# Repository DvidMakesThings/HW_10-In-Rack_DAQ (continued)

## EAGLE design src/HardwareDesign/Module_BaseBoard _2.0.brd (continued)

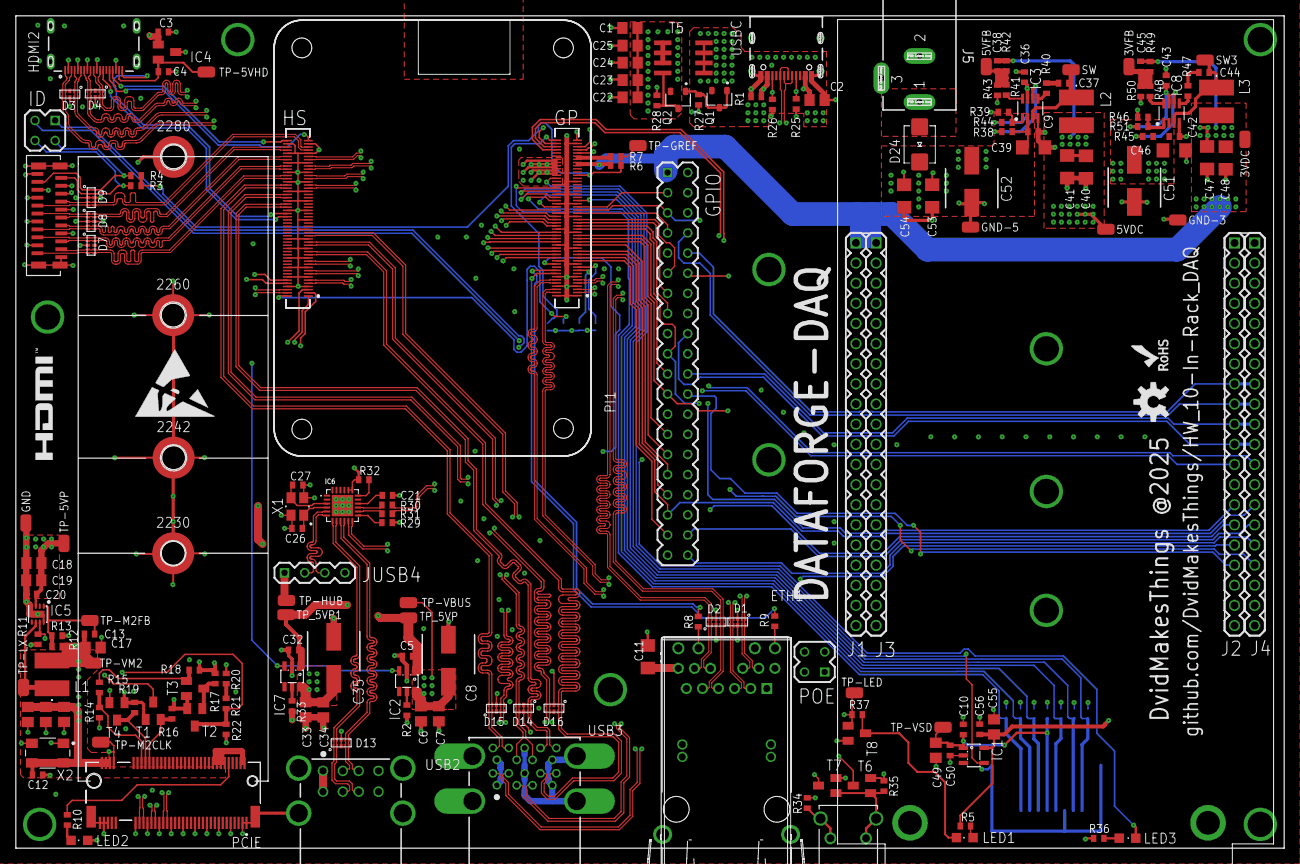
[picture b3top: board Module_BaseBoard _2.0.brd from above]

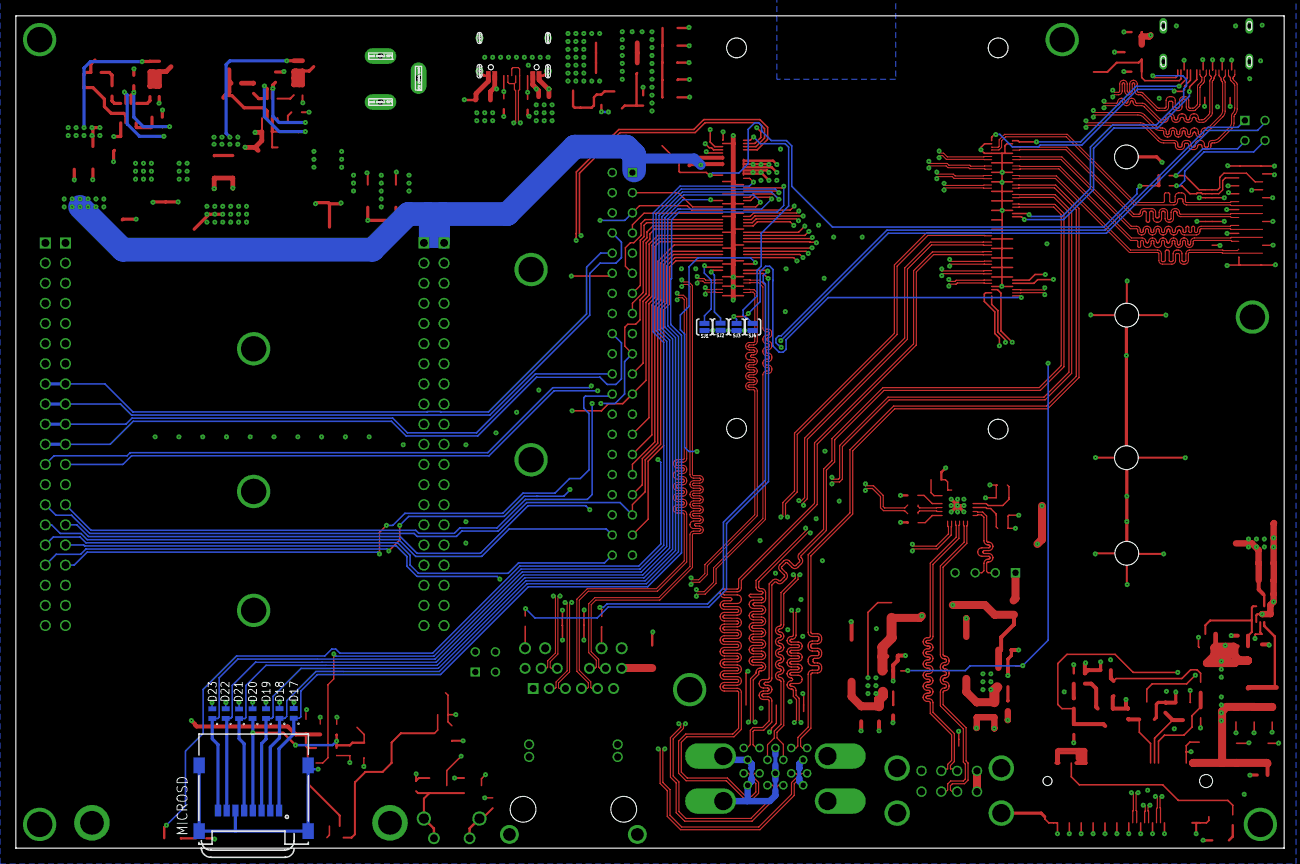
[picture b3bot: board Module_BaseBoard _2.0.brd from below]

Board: 6 copper layers, 160.0 x 105.0 mm, 198 parts (12 on the bottom side), 177 nets.

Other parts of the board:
U$1: ESD_10.00
U$2: OSHW-LOGO-M
U$3: ROHS_LOGO_0.18_IN

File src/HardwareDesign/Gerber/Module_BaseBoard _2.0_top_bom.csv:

Comment,Designator,Footprint,LCSC Part #
,IC6,QFN24,
,LED2,CHIPLED_0805,
,PI1,CM5,
0R,R6,0402,
1K,R5 R10 R34 R35 R36,0402,
2.2K,R16,0402,
2.2K 1%,R1 R3 R4 R13,0402,
2.2R,R30 R31,0402,
3.6K 1%,R21,0402,
4.2uH,L3,SRR5228A,
4.7nF,C13,C0402,
4.9uH,L2,SRR5228A,
6.8K 1%,R22,0402,
7.5K,R43 R46,0402,
9.09K,R39,0402,
10K,R14 R17 R18 R19,0402,
10K 1%,R12,0402,
10R,R40 R47,0402,
10pF,C26 C27,C0402,
10uF,C2 C6 C7 C14 C15 C16 C17 C18 C19 C23 C24 C25 C33 C34 C49,C0805,
10uF,C53,C1206,
10uF,C55,C0805,
12.7K,R50,0402,
12MHz,X1,WE-XTAL_CFPX-180,
15K 1%,R2 R33,0402,
20K,R41,0402,
22uF,C22,C0805,
22uF - 10V,C40 C41 C47 C48,C1206,
22uF 25V,C39 C46,C1206,
33K,R48,0402,
33pF,C38 C45,0402,
40.2K,R42 R49,0402,
100K,R27 R32 R44 R51,0402,
100K 1%,R11,0402,
100nF,C1,C0805,
100nF,C3 C4 C5,C0402,
100nF,C9,0402,
100nF,C10,C0402,
100nF,C11,C1206,
100nF,C12 C20 C21 C32,C0402,
100nF,C36 C37 C42 C43 C44,0402,
100nF,C50,C0402,
100nF,C54,C1206,
100nF,C56,C0402,
100uF,C51 C52,100UF-16V,
100uF 16V,C8 C35,100UF-16V,
470K,R28,0402,
470R,R8 R9,0402,
499K,R38 R45,0402,
629722000214,USBC,629722000214,
685119136923,HDMI2,685119136923,
AO4407A,T5,SO8,
AP3441SHE-7B,IC5,SON50P201X201X56-9T90X170N,
AP22653W6,IC2 IC7,SOT23-6,
BSS138,T1 T2 T3 T4 T6 T7 T8,SOT23,
CRYSTAL,X2,OSCCC500X320X130,
DNI,R7,0402,
FH12-22S-0.5SVA,DISP0,FH12-22S-0.5SH,
Green,LED1 LED3,CHIPLED_0805,
L,L1,SRR5228A,
M.2,PCIE,PCIE_M.2,
M2 x 1mm,2230 2242 2260 2280,WA-SMSI_9774010243,
MMBT3906,Q1 Q2,SOT23,
MP2315GJ-Z,IC3,SOT65P280X110-8N,
MP2315S ,IC8,SOT65P280X110-8N,
NC,R15 R20 R25 R26 R29 R37,0402,
RT9742GGJ,IC1,SOT23-5,
RT9742NGV,IC4,SOT23,
SS54B,D24,SMB,
TP,3VDC 3VFB 5VDC 5VFB GND GND-3 GND-5 SW SW3 TP-5VHD TP-5VP TP-GREF TP-HUB TP-LED TP-LX TP-M2CLK TP-M2FB TP-VBUS TP-VM2 TP-VSD TP_5VP TP_5VP1,TP,
TPD4EUSB30,D1 D2 D3 D4 D7 D8 D9 D13 D14 D15 D16,USON,

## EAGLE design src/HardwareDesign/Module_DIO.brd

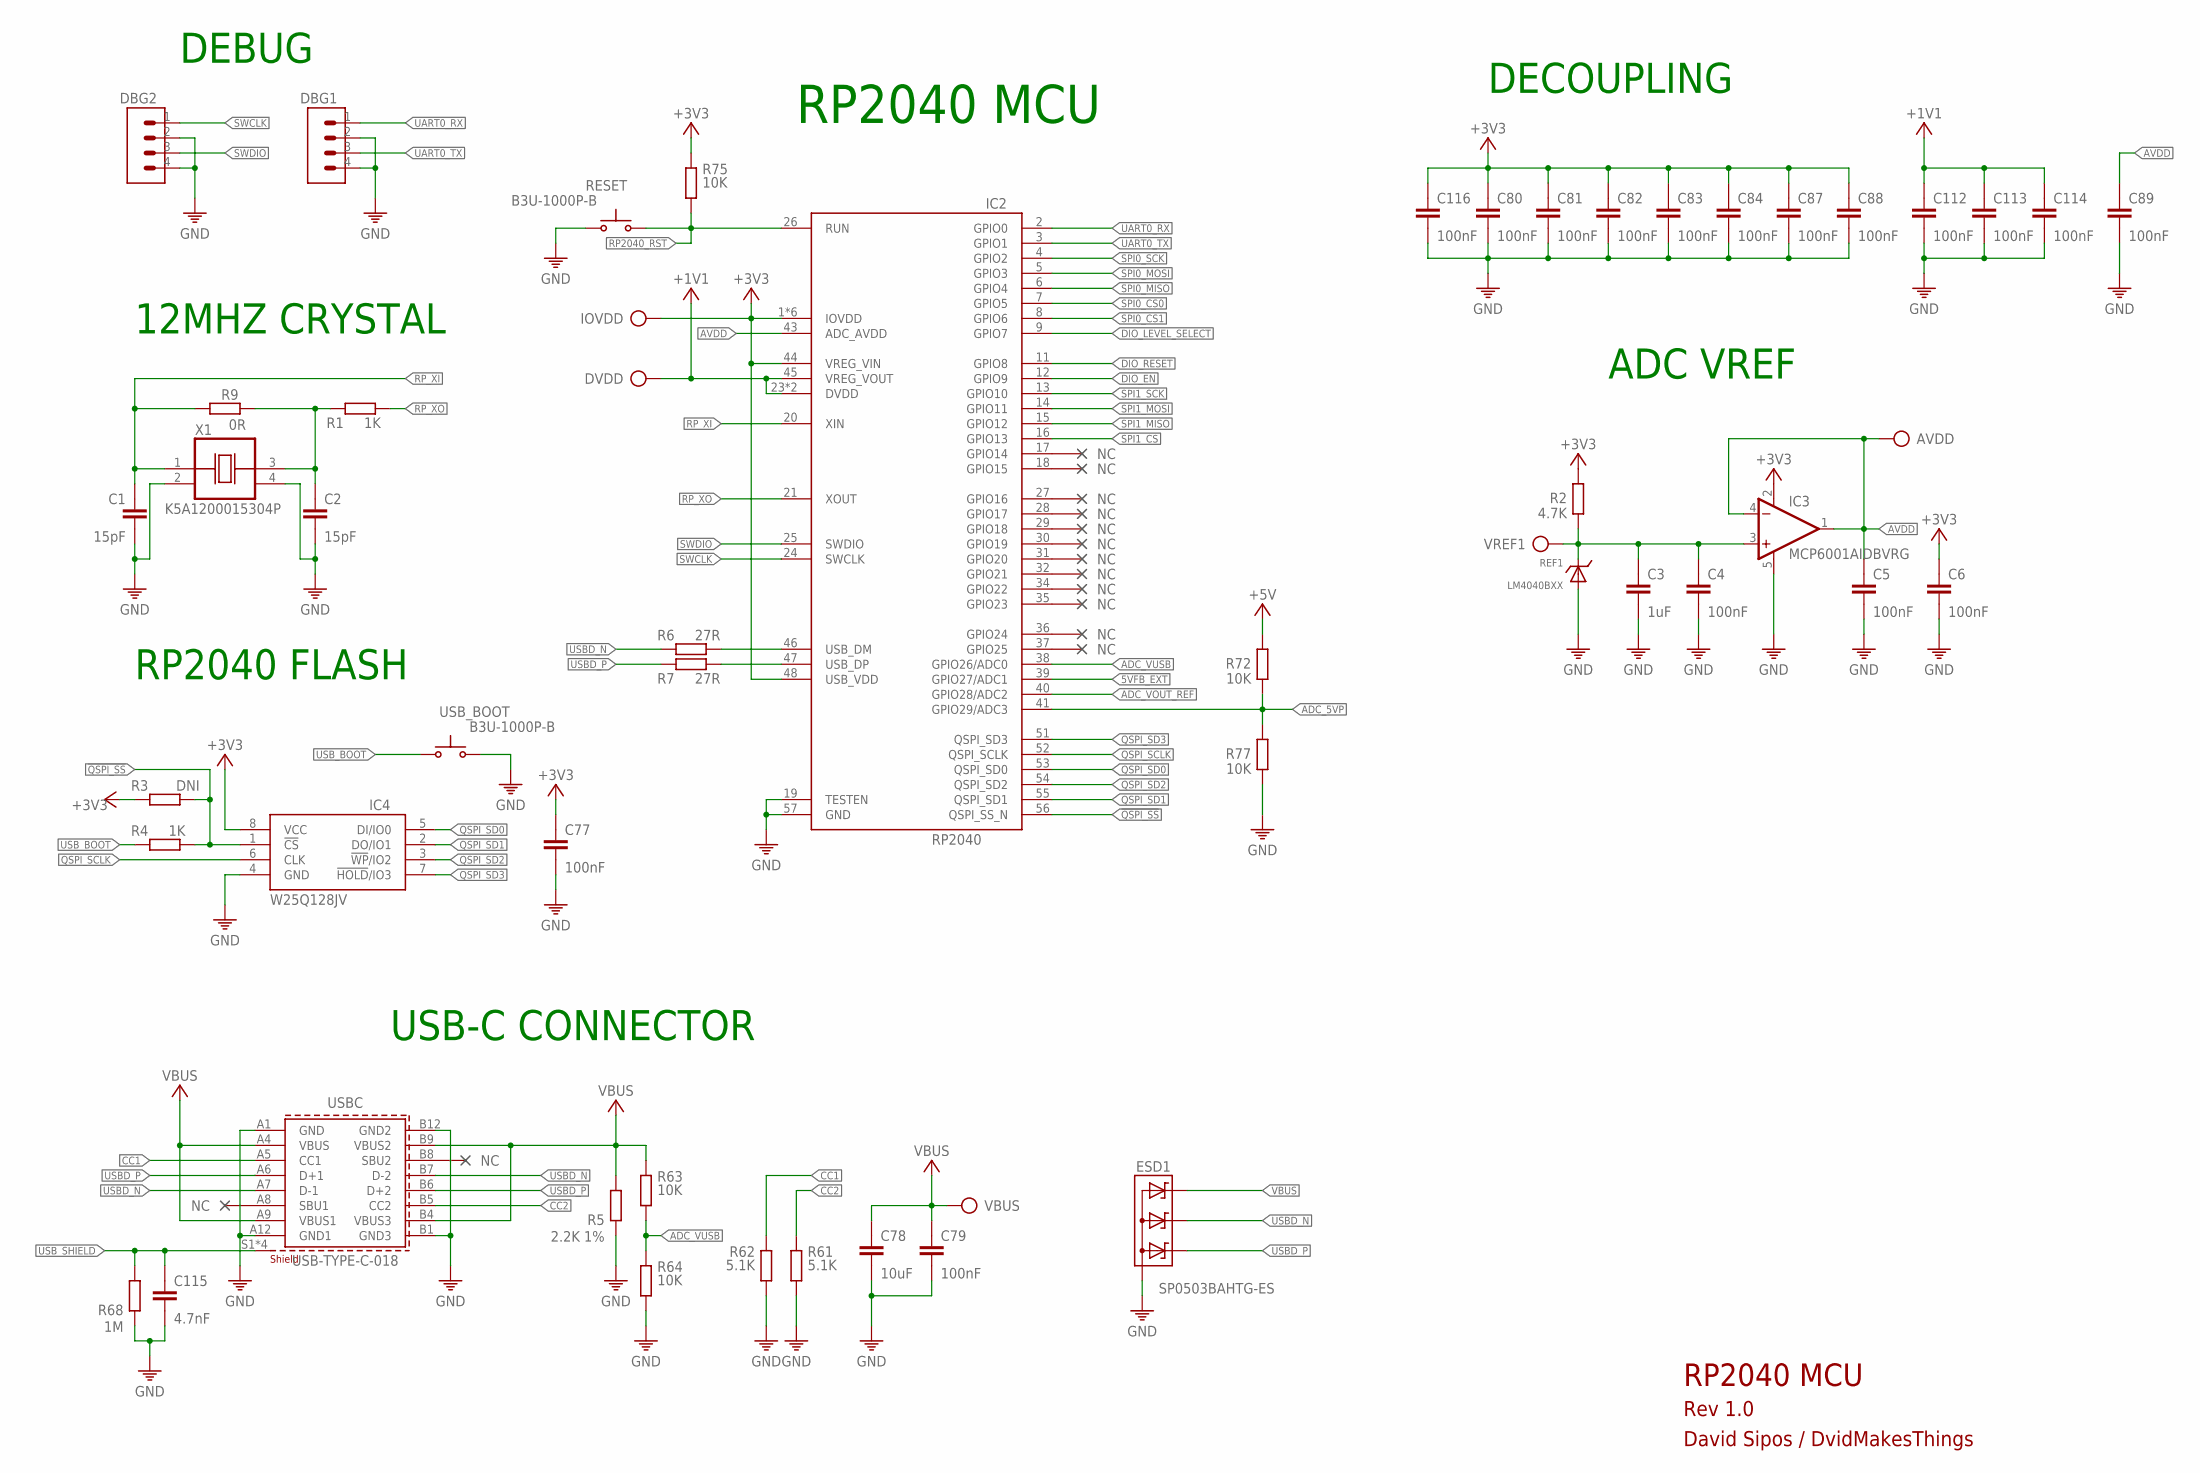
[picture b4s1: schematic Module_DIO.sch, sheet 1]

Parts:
AVDD: TP
C1, C2: 15pF; C0402
C3: 1uF; C0402
C4, C5, C6, C77, C80, C81, C82, C83, C84, C87, C88, C89, C112, C113, C114, C116: 100nF; C0402
C78: 10uF; 0805
C79: 100nF; 0402
C115: 4.7nF; 0402
DBG1, DBG2: CON-1X4; 1X4
DVDD: TP
ESD1: SP0503BAHTG-ES; SOT143
IC2: RP2040; QFN40P700X700X100-57T510
IC3: MCP6001AIDBVRG; SOT23-5
IC4: W25Q128JVPIQ; SON127P600X500X75-8N
IOVDD: TP
R1, R4: 1K; 0402
R2: 4.7K; 0402
R3: DNI; 0402
R5: 2.2K 1%; 0402
R6, R7: 27R; 0402
R9: 0R; 0402
R61, R62: 5.1K; 0402
R63, R64, R72, R75, R77: 10K; 0402
R68: 1M; 0402
REF1: LM4040BXX; SOT23
RESET: B3U-1000P-B; SWITCH-OMRON_B3U-1000P
USBC: USB-TYPE-C-018; 629722000214
USB_BOOT: B3U-1000P-B; SWITCH-OMRON_B3U-1000P
VBUS: TP
VREF1: TP
X1: K5A1200015304P; OSCCC500X320X130

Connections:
5VFB_EXT: IC2.39 (GPIO27/ADC1)
!QSPI_SS: IC2.56 (QSPI_SS_N), IC4.1 (!CS), R3.1, R4.2
+1V1: C112.1, C113.1, C114.1, DVDD.TP, IC2.23 (DVDD), IC2.45 (VREG_VOUT), IC2.50 (DVDD)
+3V3: C6.1, C77.1, C80.1, C81.1, C82.1, C83.1, C84.1, C87.1, C88.1, C116.1, IC2.1 (IOVDD), IC2.10 (IOVDD), IC2.22 (IOVDD), IC2.33 (IOVDD), IC2.42 (IOVDD), IC2.44 (VREG_VIN), IC2.48 (USB_VDD), IC2.49 (IOVDD), IC3.2 (V+), IC4.8 (VCC), IOVDD.TP, R2.2, R3.2, R75.1; also elsewhere on the board
+5V: R72.2; also elsewhere on the board
ADC_5VP: IC2.41 (GPIO29/ADC3), R72.1, R77.2
ADC_VOUT_REF: IC2.40 (GPIO28/ADC2); also elsewhere on the board
ADC_VUSB: IC2.38 (GPIO26/ADC0), R63.2, R64.1
AVDD: AVDD.TP, C5.1, C89.1, IC2.43 (ADC_AVDD), IC3.1 (OUT), IC3.4 (-IN)
CC1: R62.1, USBC.A5 (CC1)
CC2: R61.1, USBC.B5 (CC2)
DIO_EN: IC2.12 (GPIO9); also elsewhere on the board
DIO_LEVEL_SELECT: IC2.9 (GPIO7); also elsewhere on the board
DIO_RESET: IC2.11 (GPIO8); also elsewhere on the board
GND: C1.2, C2.2, C3.2, C4.2, C5.2, C6.2, C77.2, C78.2, C79.2, C80.2, C81.2, C82.2, C83.2, C84.2, C87.2, C88.2, C89.2, C112.2, C113.2, C114.2, C115.2, C116.2, DBG1.2, DBG1.4, DBG2.2, DBG2.4, ESD1.1 (A), IC2.19 (TESTEN), IC2.57 (GND), IC3.5 (V-), IC4.4 (GND), R5.2, R61.2, R62.2, R64.2, R68.2, R77.1, REF1.2 (A), REF1.3 (A), RESET.2 (S), USBC.A1 (GND), USBC.A12 (GND1), USBC.B1 (GND3), USBC.B12 (GND2), USB_BOOT.2 (S), X1.2 (VSS), X1.4 (VDD); also elsewhere on the board
unnamed: C2.1, R1.1, R9.2, X1.3 (OUT)
QSPI_SCLK: IC2.52 (QSPI_SCLK), IC4.6 (CLK)
QSPI_SD0: IC2.53 (QSPI_SD0), IC4.5 (DI/IO0)
QSPI_SD1: IC2.55 (QSPI_SD1), IC4.2 (DO/IO1)
QSPI_SD2: IC2.54 (QSPI_SD2), IC4.3 (!WP!/IO2)
QSPI_SD3: IC2.51 (QSPI_SD3), IC4.7 (!HOLD!/IO3)
RP2040_RST: IC2.26 (RUN), R75.2, RESET.1; also elsewhere on the board
RP_USBD_N: IC2.46 (USB_DM), R6.2
RP_USBD_P: IC2.47 (USB_DP), R7.2
RP_XI: C1.1, IC2.20 (XIN), R9.1, X1.1 (CON)
RP_XO: IC2.21 (XOUT), R1.2
SPI0_CS0: IC2.7 (GPIO5); also elsewhere on the board
SPI0_CS1: IC2.8 (GPIO6); also elsewhere on the board
SPI0_MISO: IC2.6 (GPIO4); also elsewhere on the board
SPI0_MOSI: IC2.5 (GPIO3); also elsewhere on the board
SPI0_SCK: IC2.4 (GPIO2); also elsewhere on the board
SPI1_CS: IC2.16 (GPIO13); also elsewhere on the board
SPI1_MISO: IC2.15 (GPIO12); also elsewhere on the board
SPI1_MOSI: IC2.14 (GPIO11); also elsewhere on the board
SPI1_SCK: IC2.13 (GPIO10); also elsewhere on the board
SWCLK: DBG2.1, IC2.24 (SWCLK); also elsewhere on the board
SWDIO: DBG2.3, IC2.25 (SWDIO); also elsewhere on the board
UART0_RX: DBG1.1, IC2.2 (GPIO0); also elsewhere on the board
UART0_TX: DBG1.3, IC2.3 (GPIO1); also elsewhere on the board
USBD_N: ESD1.3 (C2), R6.1, USBC.A7 (D-1), USBC.B7 (D-2)
USBD_P: ESD1.2 (C1), R7.1, USBC.A6 (D+1), USBC.B6 (D+2)
USB_BOOT: R4.1, USB_BOOT.1
USB_SHIELD: C115.1, R68.1, USBC.S1 (SHIELD), USBC.S2 (SHIELD), USBC.S3 (SHIELD), USBC.S4 (SHIELD)
VBUS: C78.1, C79.1, ESD1.4 (C3), R5.1, R63.1, USBC.A4 (VBUS), USBC.A9 (VBUS1), USBC.B4 (VBUS3), USBC.B9 (VBUS2), VBUS.TP; also elsewhere on the board
VREF: C3.1, C4.1, IC3.3 (+IN), R2.1, REF1.1 (C), VREF1.TP

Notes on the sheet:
USB-C CONNECTOR
DECOUPLING
12MHZ CRYSTAL
RP2040 MCU
RP2040 FLASH
ADC VREF
DEBUG
Rev 1.0
David Sipos / DvidMakesThings

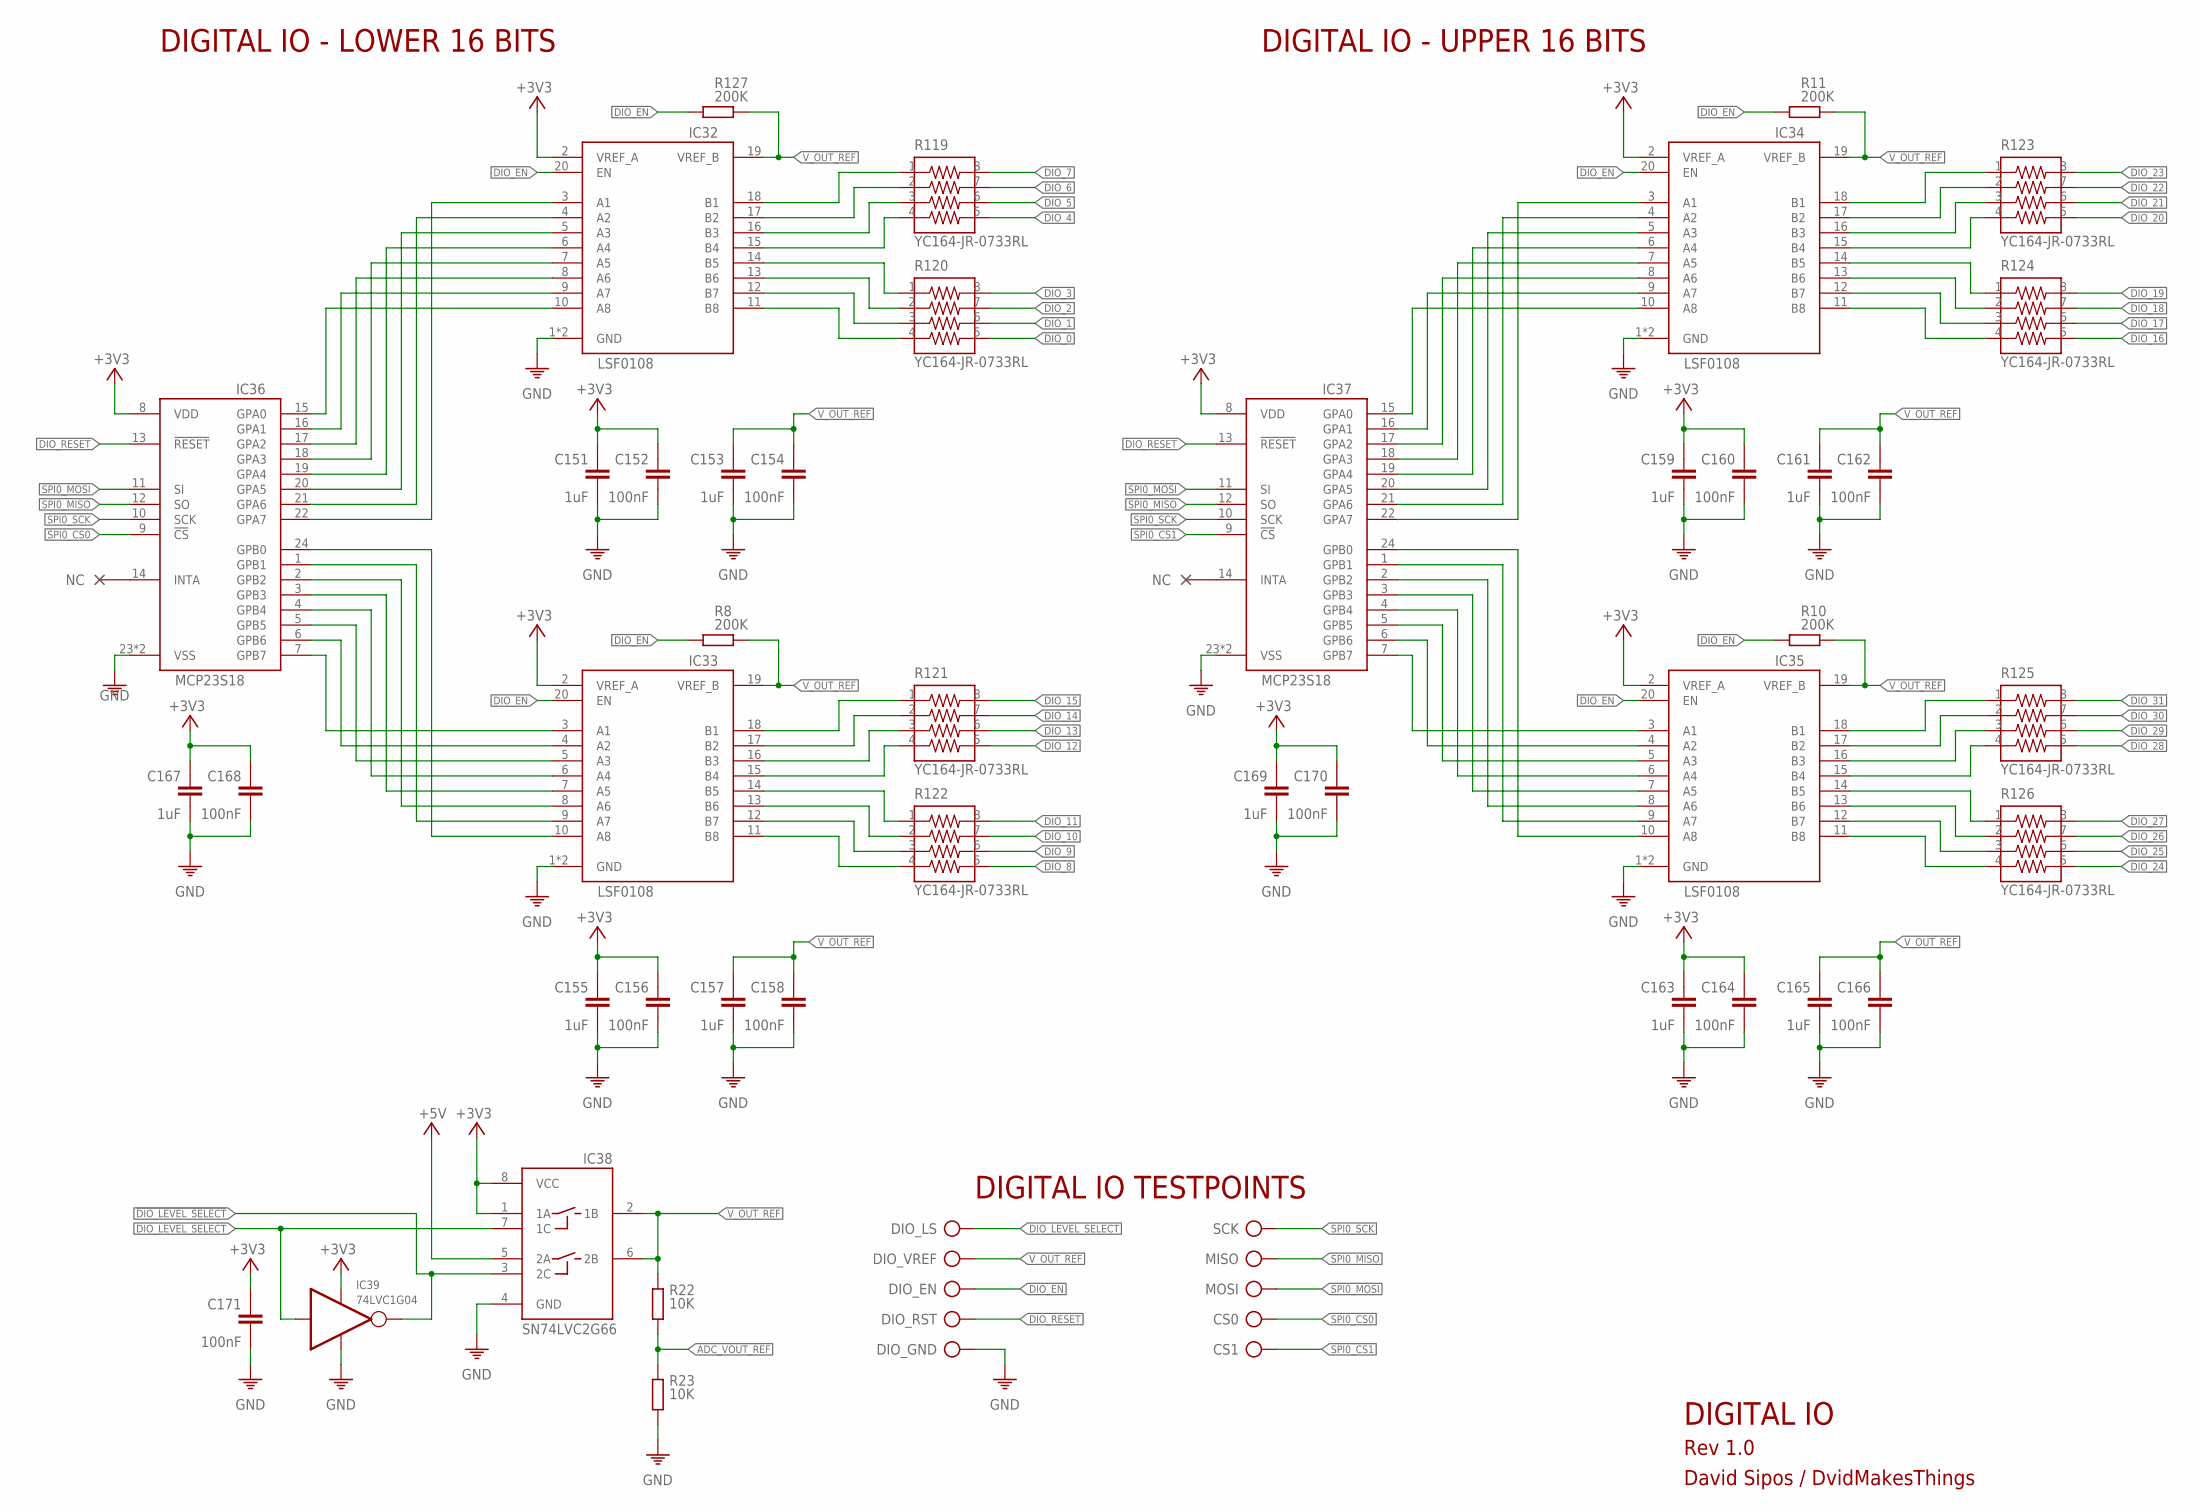
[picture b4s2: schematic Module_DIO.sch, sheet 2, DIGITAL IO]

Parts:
C151, C153, C155, C157, C159, C161, C163, C165, C167, C169: 1uF; C0402
C152, C154, C156, C158, C160, C162, C164, C166, C168, C170: 100nF; C0402
C171: 100nF; C0603
CS0, CS1: TP
DIO_EN: TP
DIO_GND: TP
DIO_LS: TP
DIO_RST: TP
DIO_VREF: TP
IC32, IC33, IC34, IC35: LSF0108; VQFN20
IC36, IC37: MCP23S18; QFN50P400X400X100-25T265
IC38: SN74LVC2G66; SOP50P310X90-8N
IC39: 74LVC1G04; SOT95P280X145-5N
MISO: TP
MOSI: TP
R8, R10, R11, R127: 200K; 0402
R22, R23: 10K; 0402
R119, R120, R121, R122, R123, R124, R125, R126: YC164-JR-0733RL
SCK: TP

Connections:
!DIO_LEVEL_SELECT: IC38.3 (2C), IC39.4 (OUT)
+3V3: C151.1, C152.1, C155.1, C156.1, C159.1, C160.1, C163.1, C164.1, C167.1, C168.1, C169.1, C170.1, C171.1, IC32.2 (VREF_A), IC33.2 (VREF_A), IC34.2 (VREF_A), IC35.2 (VREF_A), IC36.8 (VDD), IC37.8 (VDD), IC38.1 (1A), IC38.8 (VCC), IC39.5 (V+); also elsewhere on the board
+5V: IC38.5 (2A); also elsewhere on the board
ADC_VOUT_REF: R22.2, R23.1; also elsewhere on the board
DIO_0: R120.5; also elsewhere on the board
DIO_1: R120.6; also elsewhere on the board
DIO_2: R120.7; also elsewhere on the board
DIO_3: R120.8; also elsewhere on the board
DIO_4: R119.5; also elsewhere on the board
DIO_5: R119.6; also elsewhere on the board
DIO_6: R119.7; also elsewhere on the board
DIO_7: R119.8; also elsewhere on the board
DIO_8: R122.5; also elsewhere on the board
DIO_9: R122.6; also elsewhere on the board
DIO_10: R122.7; also elsewhere on the board
DIO_11: R122.8; also elsewhere on the board
DIO_12: R121.5; also elsewhere on the board
DIO_13: R121.6; also elsewhere on the board
DIO_14: R121.7; also elsewhere on the board
DIO_15: R121.8; also elsewhere on the board
DIO_16: R124.5; also elsewhere on the board
DIO_17: R124.6; also elsewhere on the board
DIO_18: R124.7; also elsewhere on the board
DIO_19: R124.8; also elsewhere on the board
DIO_20: R123.5; also elsewhere on the board
DIO_21: R123.6; also elsewhere on the board
DIO_22: R123.7; also elsewhere on the board
DIO_23: R123.8; also elsewhere on the board
DIO_24: R126.5; also elsewhere on the board
DIO_25: R126.6; also elsewhere on the board
DIO_26: R126.7; also elsewhere on the board
DIO_27: R126.8; also elsewhere on the board
DIO_28: R125.5; also elsewhere on the board
DIO_29: R125.6; also elsewhere on the board
DIO_30: R125.7; also elsewhere on the board
DIO_31: R125.8; also elsewhere on the board
DIO_EN: DIO_EN.TP, IC32.20 (EN), IC33.20 (EN), IC34.20 (EN), IC35.20 (EN), R8.2, R10.2, R11.2, R127.2; also elsewhere on the board
DIO_LEVEL_SELECT: DIO_LS.TP, IC38.7 (1C), IC39.2 (IN); also elsewhere on the board
DIO_RESET: DIO_RST.TP, IC36.13 (!RESET), IC37.13 (!RESET); also elsewhere on the board
GND: C151.2, C152.2, C153.2, C154.2, C155.2, C156.2, C157.2, C158.2, C159.2, C160.2, C161.2, C162.2, C163.2, C164.2, C165.2, C166.2, C167.2, C168.2, C169.2, C170.2, C171.2, DIO_GND.TP, IC32.1 (GND), IC32.PAD (GND), IC33.1 (GND), IC33.PAD (GND), IC34.1 (GND), IC34.PAD (GND), IC35.1 (GND), IC35.PAD (GND), IC36.23 (VSS), IC36.25 (VSS), IC37.23 (VSS), IC37.25 (VSS), IC38.4 (GND), IC39.3 (V-), R23.2; also elsewhere on the board
unnamed: IC33.9 (A7), IC36.1 (GPB1)
unnamed: IC32.10 (A8), IC36.15 (GPA0)
unnamed: IC32.9 (A7), IC36.16 (GPA1)
unnamed: IC32.8 (A6), IC36.17 (GPA2)
unnamed: IC32.7 (A5), IC36.18 (GPA3)
unnamed: IC32.6 (A4), IC36.19 (GPA4)
unnamed: IC32.5 (A3), IC36.20 (GPA5)
unnamed: IC32.4 (A2), IC36.21 (GPA6)
unnamed: IC32.3 (A1), IC36.22 (GPA7)
unnamed: IC32.18 (B1), R119.1
unnamed: IC32.17 (B2), R119.2
unnamed: IC32.16 (B3), R119.3
unnamed: IC32.15 (B4), R119.4
unnamed: IC32.14 (B5), R120.1
unnamed: IC32.13 (B6), R120.2
unnamed: IC32.12 (B7), R120.3
unnamed: IC32.11 (B8), R120.4
unnamed: IC33.10 (A8), IC36.24 (GPB0)
unnamed: IC33.8 (A6), IC36.2 (GPB2)
unnamed: IC33.7 (A5), IC36.3 (GPB3)
unnamed: IC33.6 (A4), IC36.4 (GPB4)
unnamed: IC33.5 (A3), IC36.5 (GPB5)
unnamed: IC33.4 (A2), IC36.6 (GPB6)
unnamed: IC33.3 (A1), IC36.7 (GPB7)
unnamed: IC33.18 (B1), R121.1
unnamed: IC33.17 (B2), R121.2
unnamed: IC33.16 (B3), R121.3
unnamed: IC33.15 (B4), R121.4
unnamed: IC33.14 (B5), R122.1
unnamed: IC33.13 (B6), R122.2
unnamed: IC33.12 (B7), R122.3
unnamed: IC33.11 (B8), R122.4
unnamed: IC34.10 (A8), IC37.15 (GPA0)
unnamed: IC34.9 (A7), IC37.16 (GPA1)
unnamed: IC34.8 (A6), IC37.17 (GPA2)
unnamed: IC34.7 (A5), IC37.18 (GPA3)
unnamed: IC34.6 (A4), IC37.19 (GPA4)
unnamed: IC34.5 (A3), IC37.20 (GPA5)
unnamed: IC34.4 (A2), IC37.21 (GPA6)
unnamed: IC34.3 (A1), IC37.22 (GPA7)
unnamed: IC34.18 (B1), R123.1
unnamed: IC34.17 (B2), R123.2
unnamed: IC34.16 (B3), R123.3
unnamed: IC34.15 (B4), R123.4
unnamed: IC34.14 (B5), R124.1
unnamed: IC34.13 (B6), R124.2
unnamed: IC34.12 (B7), R124.3
unnamed: IC34.11 (B8), R124.4
unnamed: IC35.8 (A6), IC37.2 (GPB2)
unnamed: IC35.7 (A5), IC37.3 (GPB3)
unnamed: IC35.6 (A4), IC37.4 (GPB4)
unnamed: IC35.5 (A3), IC37.5 (GPB5)
unnamed: IC35.4 (A2), IC37.6 (GPB6)
unnamed: IC35.3 (A1), IC37.7 (GPB7)
unnamed: IC35.9 (A7), IC37.1 (GPB1)
unnamed: IC35.10 (A8), IC37.24 (GPB0)
unnamed: IC35.18 (B1), R125.1
unnamed: IC35.17 (B2), R125.2
unnamed: IC35.16 (B3), R125.3
unnamed: IC35.15 (B4), R125.4
unnamed: IC35.14 (B5), R126.1
unnamed: IC35.13 (B6), R126.2
unnamed: IC35.12 (B7), R126.3
unnamed: IC35.11 (B8), R126.4
SPI0_CS0: CS0.TP, IC36.9 (!CS); also elsewhere on the board
SPI0_CS1: CS1.TP, IC37.9 (!CS); also elsewhere on the board
SPI0_MISO: IC36.12 (SO), IC37.12 (SO), MISO.TP; also elsewhere on the board
SPI0_MOSI: IC36.11 (SI), IC37.11 (SI), MOSI.TP; also elsewhere on the board
SPI0_SCK: IC36.10 (SCK), IC37.10 (SCK), SCK.TP; also elsewhere on the board
V_OUT_REF: C153.1, C154.1, C157.1, C158.1, C161.1, C162.1, C165.1, C166.1, DIO_VREF.TP, IC32.19 (VREF_B), IC33.19 (VREF_B), IC34.19 (VREF_B), IC35.19 (VREF_B), IC38.2 (1B), IC38.6 (2B), R8.1, R10.1, R11.1, R22.1, R127.1

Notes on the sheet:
DIGITAL IO - LOWER 16 BITS
DIGITAL IO - UPPER 16 BITS
DIGITAL IO TESTPOINTS
DIGITAL IO
Rev 1.0
David Sipos / DvidMakesThings

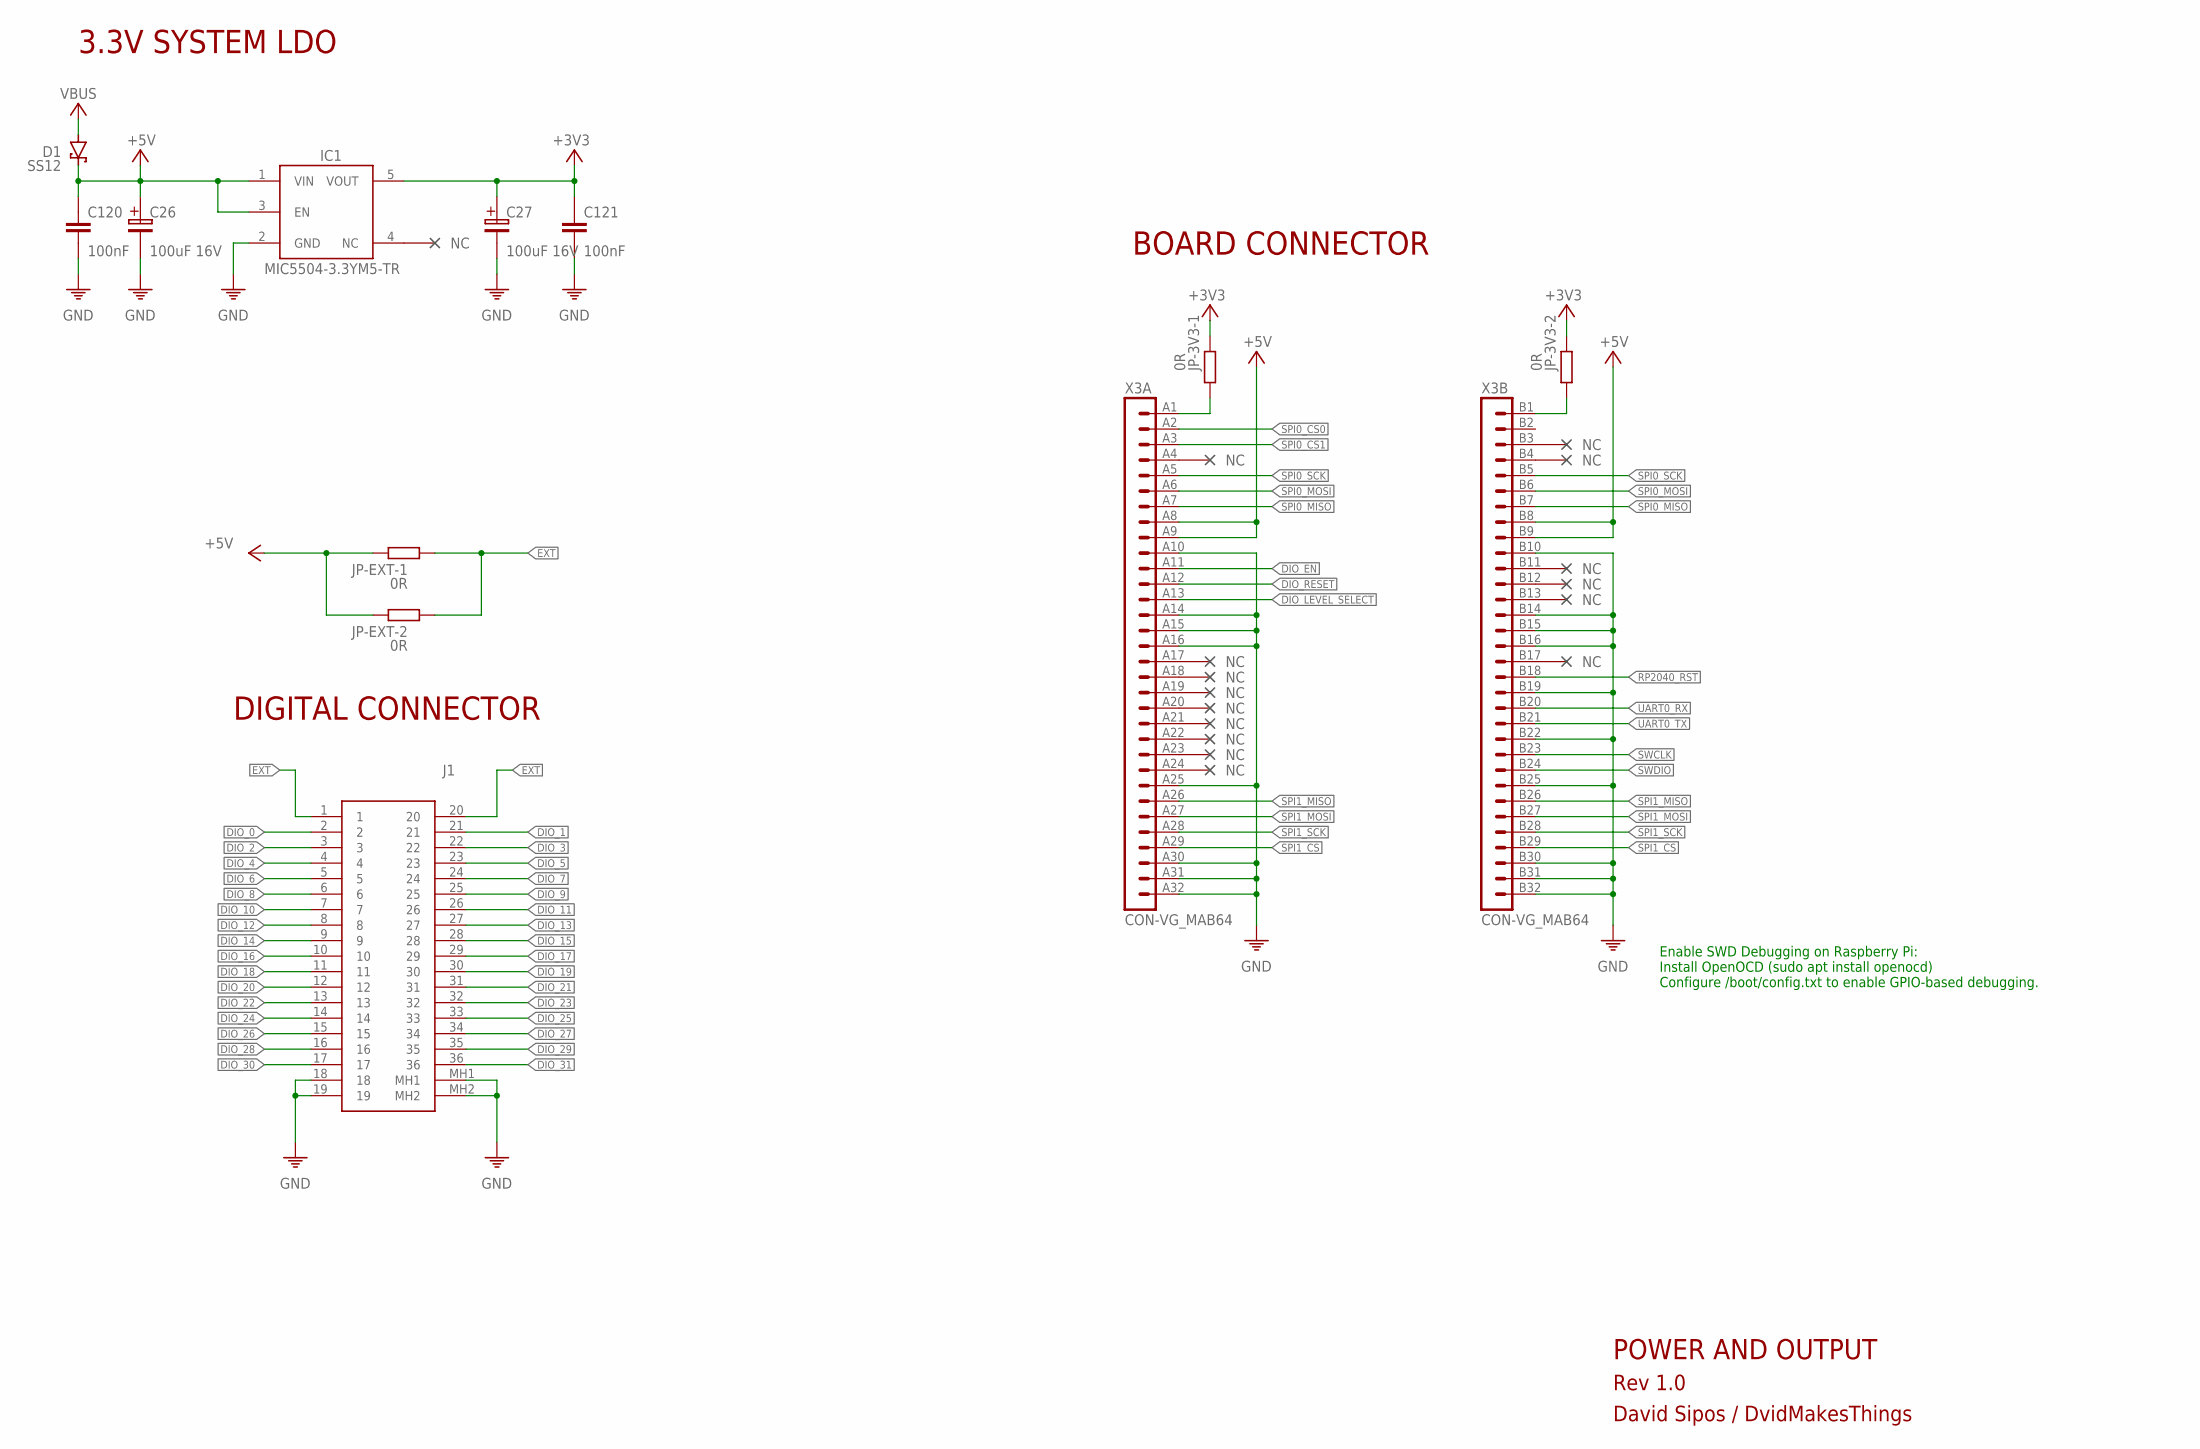
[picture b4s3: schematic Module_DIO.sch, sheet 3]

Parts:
C26, C27: 100uF 16V; 100UF-16V
C120, C121: 100nF; C0402
D1: SS12; SMA
IC1: MIC5504-3.3YM5-TR; SOT23-5
J1: N10236-52B3PC; MDB36
JP-3V3-1, JP-3V3-2: 0R; 0603
JP-EXT-1, JP-EXT-2: 0R; 0603
X3: CON-VG_MAB64

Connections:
+3V3: C27.1, C121.1, IC1.5 (VOUT), JP-3V3-1.1, JP-3V3-2.1; also elsewhere on the board
+5V: C26.1, C120.1, D1.C, IC1.1 (VIN), IC1.3 (EN), JP-EXT-1.1, JP-EXT-2.1, X3.A8 (8), X3.A9 (9), X3.B8 (8), X3.B9 (9); also elsewhere on the board
DIO_0: J1.2; also elsewhere on the board
DIO_1: J1.21; also elsewhere on the board
DIO_2: J1.3; also elsewhere on the board
DIO_3: J1.22; also elsewhere on the board
DIO_4: J1.4; also elsewhere on the board
DIO_5: J1.23; also elsewhere on the board
DIO_6: J1.5; also elsewhere on the board
DIO_7: J1.24; also elsewhere on the board
DIO_8: J1.6; also elsewhere on the board
DIO_9: J1.25; also elsewhere on the board
DIO_10: J1.7; also elsewhere on the board
DIO_11: J1.26; also elsewhere on the board
DIO_12: J1.8; also elsewhere on the board
DIO_13: J1.27; also elsewhere on the board
DIO_14: J1.9; also elsewhere on the board
DIO_15: J1.28; also elsewhere on the board
DIO_16: J1.10; also elsewhere on the board
DIO_17: J1.29; also elsewhere on the board
DIO_18: J1.11; also elsewhere on the board
DIO_19: J1.30; also elsewhere on the board
DIO_20: J1.12; also elsewhere on the board
DIO_21: J1.31; also elsewhere on the board
DIO_22: J1.13; also elsewhere on the board
DIO_23: J1.32; also elsewhere on the board
DIO_24: J1.14; also elsewhere on the board
DIO_25: J1.33; also elsewhere on the board
DIO_26: J1.15; also elsewhere on the board
DIO_27: J1.34; also elsewhere on the board
DIO_28: J1.16; also elsewhere on the board
DIO_29: J1.35; also elsewhere on the board
DIO_30: J1.17; also elsewhere on the board
DIO_31: J1.36; also elsewhere on the board
DIO_EN: X3.A11 (11); also elsewhere on the board
DIO_LEVEL_SELECT: X3.A13 (13); also elsewhere on the board
DIO_RESET: X3.A12 (12); also elsewhere on the board
EXT: J1.1, J1.20, JP-EXT-1.2, JP-EXT-2.2
GND: C26.2, C27.2, C120.2, C121.2, IC1.2 (GND), J1.18, J1.19, J1.MH1, J1.MH2, X3.A10 (10), X3.A14 (14), X3.A15 (15), X3.A16 (16), X3.A25 (25), X3.A30 (30), X3.A31 (31), X3.A32 (32), X3.B10 (10), X3.B14 (14), X3.B15 (15), X3.B16 (16), X3.B19 (19), X3.B22 (22), X3.B25 (25), X3.B30 (30), X3.B31 (31), X3.B32 (32); also elsewhere on the board
unnamed: JP-3V3-2.2, X3.B1 (1)
unnamed: JP-3V3-1.2, X3.A1 (1)
RP2040_RST: X3.B18 (18); also elsewhere on the board
SPI0_CS0: X3.A2 (2); also elsewhere on the board
SPI0_CS1: X3.A3 (3); also elsewhere on the board
SPI0_MISO: X3.A7 (7), X3.B7 (7); also elsewhere on the board
SPI0_MOSI: X3.A6 (6), X3.B6 (6); also elsewhere on the board
SPI0_SCK: X3.A5 (5), X3.B5 (5); also elsewhere on the board
SPI1_CS: X3.A29 (29), X3.B29 (29); also elsewhere on the board
SPI1_MISO: X3.A26 (26), X3.B26 (26); also elsewhere on the board
SPI1_MOSI: X3.A27 (27), X3.B27 (27); also elsewhere on the board
SPI1_SCK: X3.A28 (28), X3.B28 (28); also elsewhere on the board
SWCLK: X3.B23 (23); also elsewhere on the board
SWDIO: X3.B24 (24); also elsewhere on the board
UART0_RX: X3.B20 (20); also elsewhere on the board
UART0_TX: X3.B21 (21); also elsewhere on the board
VBUS: D1.A; also elsewhere on the board

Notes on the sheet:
3.3V SYSTEM LDO
Enable SWD Debugging on Raspberry Pi: Install OpenOCD (sudo apt install openocd) Configure /boot/config.txt to enable GPIO-based debugging.
BOARD CONNECTOR
DIGITAL CONNECTOR
POWER AND OUTPUT
Rev 1.0
David Sipos / DvidMakesThings

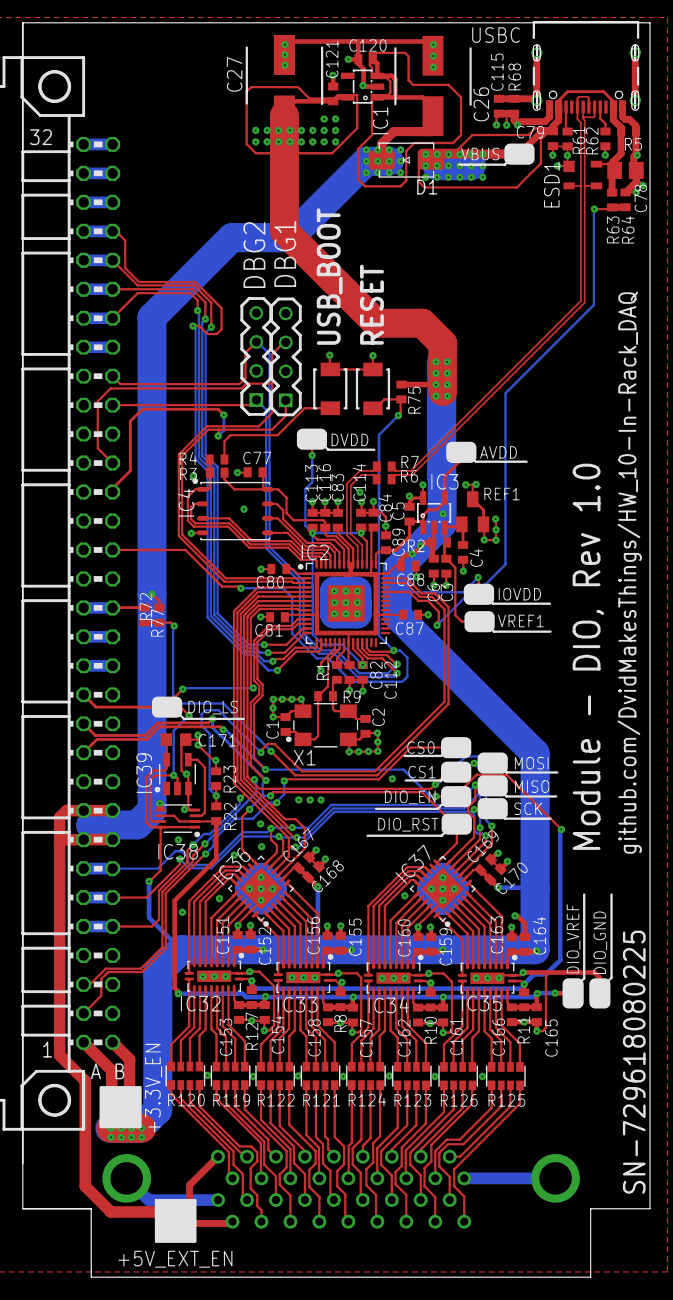
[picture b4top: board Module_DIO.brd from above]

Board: 4 copper layers, 55.0 x 110.0 mm, 119 parts (1 on the bottom side), 145 nets.

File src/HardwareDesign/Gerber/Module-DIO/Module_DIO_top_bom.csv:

Comment,Designator,Footprint,LCSC Part #
0R,JP-3V3-1 JP-3V3-2 JP-EXT-1 JP-EXT-2,0603,
0R,R9,0402,
1K,R1 R4,0402,
1M,R68,0402,
1uF,C3 C151 C153 C155 C157 C159 C161 C163 C165 C167 C169,C0402,
2.2K 1%,R5,0402,
4.7K,R2,0402,
4.7nF,C115,0402,
5.1K,R61 R62,0402,
10K,R22 R23 R63 R64 R72 R75 R77,0402,
10uF,C78,0805,
15pF,C1 C2,C0402,
27R,R6 R7,0402,
74LVC1G04,IC39,SOT95P280X145-5N,
100nF,C4 C5 C6 C77,C0402,
100nF,C79,0402,
100nF,C80 C81 C82 C83 C84 C87 C88 C89 C112 C113 C114 C116 C120 C121 C152 C154 C156 C158 C160 C162 C164 C166 C168 C170,C0402,
100nF,C171,C0603,
100uF 16V,C26 C27,100UF-16V,
200K,R8 R10 R11 R127,0402,
B3U-1000P-B,RESET USB_BOOT,SWITCH-OMRON_B3U-1000P,
DNI,R3,0402,
K5A1200015304P,X1,OSCCC500X320X130,
LM4040BXX,REF1,SOT23,
LSF0108,IC32 IC33 IC34 IC35,VQFN20,
MCP23S18,IC36 IC37,QFN50P400X400X100-25T265,
MCP6001AIDBVRG,IC3,SOT23-5,
MIC5504-3.3YM5-TR,IC1,SOT23-5,
RP2040,IC2,QFN40P700X700X100-57T510,
SN74LVC2G66,IC38,SOP50P310X90-8N,
SP0503BAHTG-ES,ESD1,SOT143,
SS12,D1,SMA,
TP,AVDD CS0 CS1 DIO_EN DIO_GND DIO_LS DIO_RST DIO_VREF DVDD IOVDD MISO MOSI SCK VBUS VREF1,TP,
USB-TYPE-C-018,USBC,629722000214,
W25Q128JVPIQ,IC4,SON127P600X500X75-8N,
YC164-JR-0733RL,R119 R120 R121 R122 R123 R124 R125 R126,YC164-JR-0733RL,
